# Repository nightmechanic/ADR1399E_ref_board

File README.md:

# ADR1399E Voltage reference circuit

This is a **hobby grade** 10V (well, close to...) voltage refernce based on Analog Devices' ADR1399E reference.
It can be powered with either 5V USB (using a boost switching regulator) , or a 5S Li-Ion pack (or equivalent)

*(Kicad rendering of the board)*

## Source:
Mostly based on: https://www.eevblog.com/forum/metrology/lm399-based-10-v-reference/ (specifically replies starting from 1300 to about 1343)

## Notes:
Designed in KiCad (9.0)

### Enclosure:
3D printable 2-piece enclosure design in [onshape](https://cad.onshape.com/documents/444727e948f9e5cc4e41eae1/w/781dc2eb3e355c2d7b923edf/e/b0f13c680a3e4fdfcef48c95?renderMode=0&rightPanel=namedPositionPanel&uiState=685cefcc24538942f7012c4b)

- Designed to use (4) M3x5x4 ("Voron") threaded inserts and (4) m3x20 screws for securing the base and lid together 
- With 4mm and 2mm Banana socket pairs
- With an (optional) internal refernce covers (identical top and bottom), to, somewhat, thermally isolate the refernce "island" from the rest 

Note that top/lid 3D printing may require supports for the screw head recesses
Printing the internal refernce cover will need supports

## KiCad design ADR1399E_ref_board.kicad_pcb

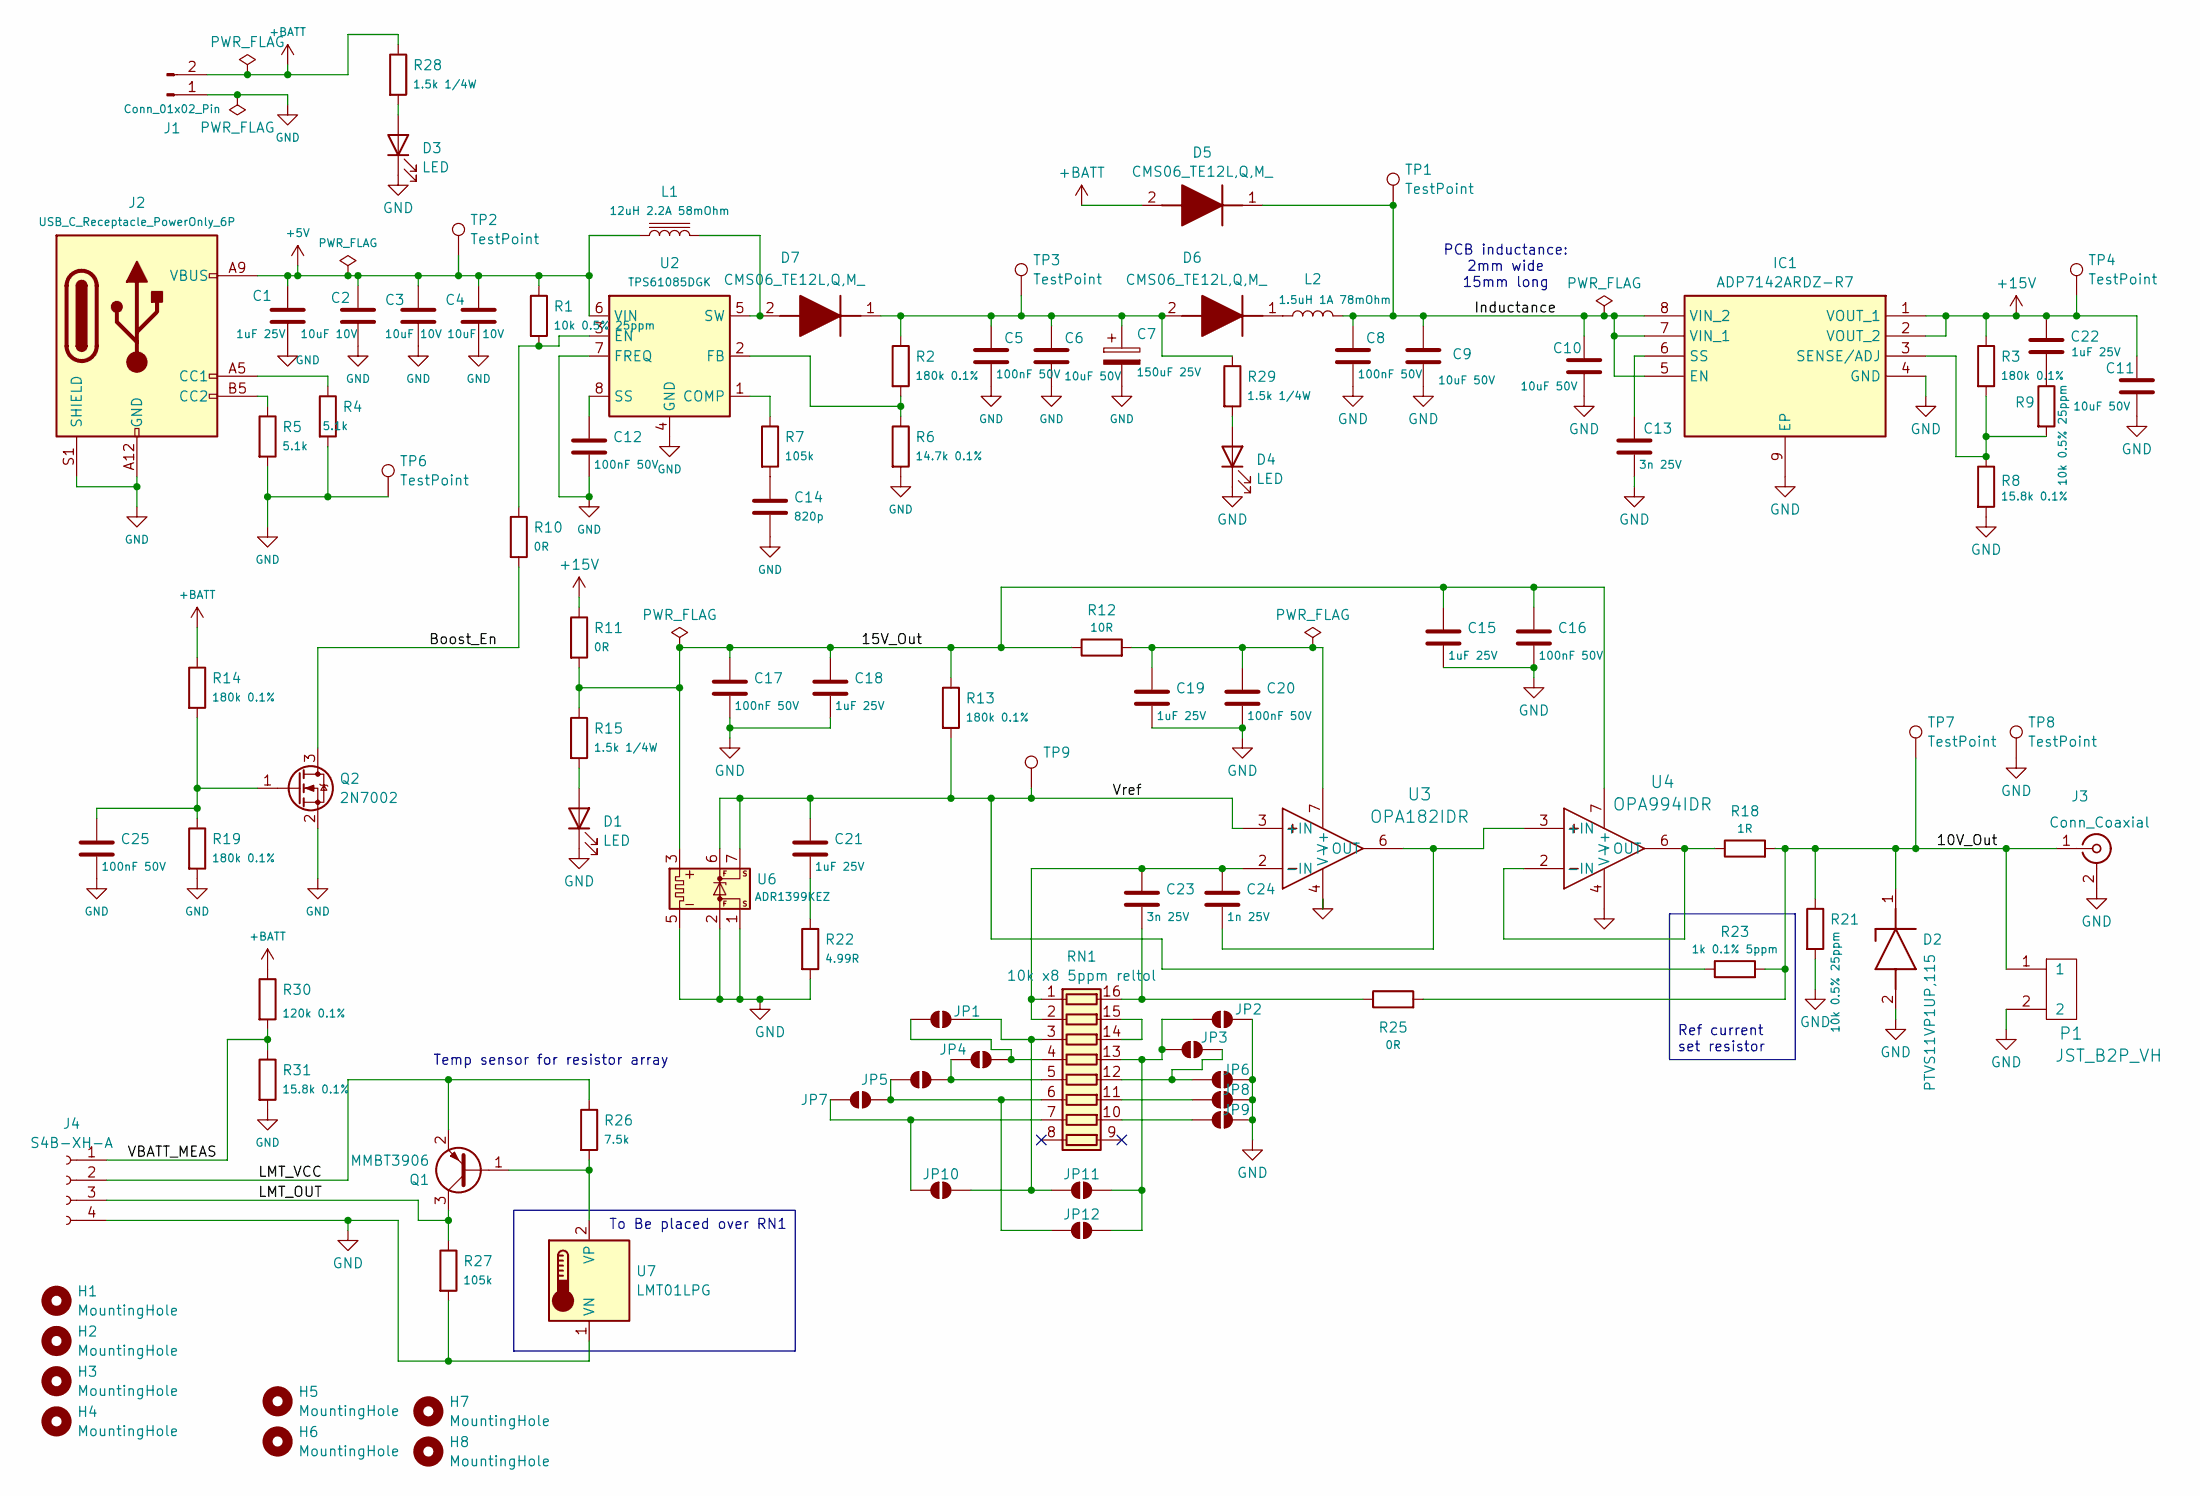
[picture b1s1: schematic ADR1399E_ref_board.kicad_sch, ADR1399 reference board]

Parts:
C1, C15, C18, C19, C21, C22: 1uF 25V; C_0603_1608Metric_Pad1.08x0.95mm_HandSolder; Manufacturer_Part_Number TMK107ABJ225KA-T
C2, C3, C4: 10uF 10V; C_0805_2012Metric_Pad1.18x1.45mm_HandSolder; Manufacturer_Part_Number CL21A106KPFNNNG
C5, C8, C12, C16, C17, C20, C25: 100nF 50V; C_0603_1608Metric_Pad1.08x0.95mm_HandSolder; Manufacturer_Part_Number CL10B104KB8NNWC
C6, C9, C10, C11: 10uF 50V; C_1210_3225Metric_Pad1.33x2.70mm_HandSolder; Manufacturer_Part_Number CL32A106KBJNNNE
C7: 150uF 25V; CP_Elec_8x6.7; Manufacturer_Part_Number A768KE157M1ELAE029
C13, C23: 3n 25V; C_0603_1608Metric_Pad1.08x0.95mm_HandSolder; Manufacturer_Part_Number GCM1885C1H302JA16D
C14: 820p; C_0603_1608Metric_Pad1.08x0.95mm_HandSolder; Manufacturer_Part_Number CC0603JRNPO9BN821
C24: 1n 25V; C_0603_1608Metric_Pad1.08x0.95mm_HandSolder; Manufacturer_Part_Number C0603C102J5GAC7411
D1, D3, D4: LED; LED_1206_3216Metric_Pad1.42x1.75mm_HandSolder; Manufacturer_Part_Number IN-S126ATA
D2: PTVS11VP1UP,115; PMEG3050EP115; Mouser Part Number 771-PTVS11VP1UP115
D5, D6, D7: CMS06_TE12L,Q,M_; SODFL4724X108N; Mouser Part Number 757-CMS06TE12L,Q,M
H1, H2, H3, H4: MountingHole; MountingHole_3.2mm_M3_ISO7380
H5, H6, H7, H8: MountingHole; MountingHole_2.2mm_M2
IC1: ADP7142ARDZ-R7; SOIC-8-1EP_3.9x4.9mm_P1.27mm_EP2.29x3mm_ThermalVias; Mouser Part Number 584-ADP7118ARDZ-R7
J1: Conn_01x02_Pin; AMASS_XT30PW-M_1x02_P2.50mm_Horizontal
J2: USB_C_Receptacle_PowerOnly_6P; USB_C_Receptacle_GCT_USB4125-xx-x-0190_6P_TopMnt_Horizontal; Manufacturer_Part_Number USB4125-GF-A-0190
J3: Conn_Coaxial; SMA_Molex_73251-1153_EdgeMount_Horizontal; Manufacturer_Part_Number 73251-1150
J4: S4B-XH-A; JST_XH_S4B-XH-A-1_1x04_P2.50mm_Horizontal; Manufacturer_Part_Number S4B-XH-A-GU
JP1, JP2, JP3, JP4, JP5, JP6, JP7, JP8, JP9, JP10, JP11, JP12: SolderJumper_2_Open; SolderJumper-2_P1.3mm_Open_RoundedPad1.0x1.5mm
L1: 12uH 2.2A 58mOhm; ASPI-6045S; Manufacturer_Part_Number ASPI-6045S-120M-T
L2: 1.5uH 1A 78mOhm; L_1210_3225Metric_Pad1.42x2.65mm_HandSolder; Manufacturer_Part_Number LBC3225T1R5MR
P1: JST_B2P_VH; JST_VH_B2P-VH_1x02_P3.96mm_Vertical; Manufacturer_Part_Number B2P-VH-GU
Q1: MMBT3906; SOT-23; Manufacturer_Part_Number MMBT3906LT1G
Q2: 2N7002; SOT-23
R1, R9, R21: 10k 0.5% 25ppm; R_0603_1608Metric_Pad0.98x0.95mm_HandSolder; Manufacturer_Part_Number MCT06030D1002DP500
R2, R3, R13, R14, R19: 180k 0.1%; R_0603_1608Metric_Pad0.98x0.95mm_HandSolder; Manufacturer_Part_Number ERA-3AEB184V
R4, R5: 5.1k; R_0603_1608Metric_Pad0.98x0.95mm_HandSolder; Manufacturer_Part_Number RG1608P-512-D-T5
R6: 14.7k 0.1%; R_0603_1608Metric_Pad0.98x0.95mm_HandSolder; Manufacturer_Part_Number ERA-3AEB1782V
R7, R27: 105k; R_0603_1608Metric_Pad0.98x0.95mm_HandSolder; Manufacturer_Part_Number RT0603DRD07105KL
R8: 15.8k 0.1%; R_0603_1608Metric_Pad0.98x0.95mm_HandSolder; Manufacturer_Part_Number RG1608P-512-D-T5
R10, R11, R25: 0R; R_0805_2012Metric_Pad1.20x1.40mm_HandSolder; Manufacturer_Part_Number MCU0805MZ0000ZP500
R12: 10R; R_0805_2012Metric_Pad1.20x1.40mm_HandSolder; Manufacturer_Part_Number RR1220Q-100-D
R15, R28, R29: 1.5k 1/4W; R_1206_3216Metric_Pad1.30x1.75mm_HandSolder; Manufacturer_Part_Number RNCP1206FTD1K50
R18: 1R; R_0805_2012Metric_Pad1.20x1.40mm_HandSolder; Manufacturer_Part_Number RT0805BRD071RL
R22: 4.99R; R_0603_1608Metric_Pad0.98x0.95mm_HandSolder; Manufacturer_Part_Number RT0603DRE074R99L
R23: 1k 0.1% 5ppm; R_0603_1608Metric_Pad0.98x0.95mm_HandSolder; Manufacturer_Part_Number PCF0603-13-1K0BT1
R26: 7.5k; R_0603_1608Metric_Pad0.98x0.95mm_HandSolder; Manufacturer_Part_Number RT0603FRE077K5L
R30: 120k 0.1%; R_0603_1608Metric_Pad0.98x0.95mm_HandSolder; Manufacturer_Part_Number ERA-3AEB124V
R31: 15.8k 0.1%; R_0603_1608Metric_Pad0.98x0.95mm_HandSolder; Manufacturer_Part_Number ERA-3AEB1782V
RN1: 10k x8 5ppm reltol; SO-16_3.9x9.9mm_P1.27mm; Manufacturer_Part_Number NOMCT16031002AT1
TP1, TP2, TP3, TP4, TP6, TP7, TP8, TP9: TestPoint; TestPoint_Loop_D1.80mm_Drill1.0mm_Beaded
U2: TPS61085DGK; VSSOP-8_3x3mm_P0.65mm; Manufacturer_Part_Number TPS61085DGKR
U3: OPA182IDR; D0008A-IPC_A; Manufacturer_Part_Number OPA182IDR
U4: OPA994IDR; D0008A-IPC_A; Manufacturer_Part_Number OPA994IDR
U6: ADR1399KEZ; Analog_LCC-8_5x5mm_P1.27mm; Manufacturer_Part_Number ADR1399KEZ
U7: LMT01LPG; LMT01LPG_LPG0002A; Manufacturer_Part_Number LMT01LPGM

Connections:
+5V: C1.1, C2.1, C3.1, C4.1, J2.A9 (VBUS), J2.B9 (VBUS), L1.1, R1.1, TP2.1, U2.6 (VIN)
+15V: C11.1, C22.1, IC1.1 (VOUT_1), IC1.2 (VOUT_2), R3.1, R11.1, TP4.1
+BATT: D5.2 (A), J1.2, R14.1, R28.1, R30.1
/10V_Out: D2.1 (K), J3.1 (In), P1.1, R18.2, R21.1, R23.2, R25.2, TP7.1
/15V_Out: C15.1, C16.1, C17.1, C18.1, R11.2, R12.1, R13.1, R15.1, U4.7 (V+), U6.3 (HEATER+)
/Boost_En: Q2.3 (D), R10.2
/Inductance: C8.1, C9.1, C10.1, D5.1 (K), IC1.5 (EN), IC1.7 (VIN_1), IC1.8 (VIN_2), L2.2, TP1.1
/LMT_OUT: J4.3, Q1.3 (C), R27.1
/LMT_VCC: J4.2, Q1.2 (E), R26.1
/VBATT_MEAS: J4.1, R30.2, R31.1
/Vref: C21.1, R13.2, R23.1, TP9.1, U3.3 (+IN), U6.6 (+REFF), U6.7 (+REFS)
GND: C1.2, C2.2, C3.2, C4.2, C5.2, C6.2, C7.2, C8.2, C9.2, C10.2, C11.2, C12.2, C13.2, C14.2, C15.2, C16.2, C17.2, C18.2, C19.2, C20.2, C25.2, D1.1 (K), D2.2 (A), D3.1 (K), D4.1 (K), IC1.4 (GND), IC1.9 (EP), J1.1, J2.A12 (GND), J2.B12 (GND), J2.S1 (SHIELD), J3.2 (Ext), J4.4, JP2.2 (B), JP6.2 (B), JP8.2 (B), JP9.2 (B), P1.2, Q2.2 (S), R4.2, R5.2, R6.2, R8.2, R19.2, R21.2, R22.2, R27.2, R31.2, TP6.1, TP8.1, U2.4 (GND), U2.7 (FREQ), U3.4 (V-), U4.4 (V-), U6.1 (-REFS), U6.2 (-REFF), U6.5 (HEATER-), U7.1 (VN)
unnamed: C14.1, R7.2
unnamed: C21.2, R22.1
unnamed: C22.2, R9.1
unnamed: D1.2 (A), R15.2
unnamed: D3.2 (A), R28.2
unnamed: D4.2 (A), R29.2
unnamed: C5.1, C6.1, C7.1, D6.2 (A), D7.1 (K), R2.1, R29.1, TP3.1
unnamed: D6.1 (K), L2.1
unnamed: D7.2 (A), L1.2, U2.5 (SW)
unnamed: IC1.3 (SENSE/ADJ), R3.2, R8.1, R9.2
unnamed: C13.1, IC1.6 (SS)
unnamed: J2.A5 (CC1), R4.1
unnamed: J2.B5 (CC2), R5.1
unnamed: JP1.1 (A), JP4.2 (B), RN1.4 (R4.1)
unnamed: JP1.2 (B), JP10.2 (B), JP11.1 (A), RN1.3 (R3.1)
unnamed: JP3.2 (B), JP6.1 (A), RN1.12 (R5.2)
unnamed: JP4.1 (A), JP5.2 (B), RN1.5 (R5.1)
unnamed: JP8.1 (A), RN1.11 (R6.2)
unnamed: JP9.1 (A), RN1.10 (R7.2)
unnamed: JP7.1 (A), JP10.1 (A), RN1.7 (R7.1)
unnamed: JP2.1 (A), JP3.1 (A), JP11.2 (B), JP12.2 (B), RN1.13 (R4.2)
unnamed: JP5.1 (A), JP7.2 (B), JP12.1 (A), RN1.6 (R6.1)
unnamed: Q1.1 (B), R26.2, U7.2 (VP)
unnamed: C25.1, Q2.1 (G), R14.2, R19.1
unnamed: C23.1, C24.1, RN1.1 (R1.1), RN1.2 (R2.1), U3.2 (-IN)
unnamed: C23.2, R25.1, RN1.16 (R1.2)
unnamed: RN1.14 (R3.2), RN1.15 (R2.2)
unnamed: R7.1, U2.1 (COMP)
unnamed: R1.2, R10.1, U2.3 (EN)
unnamed: R2.2, R6.1, U2.2 (FB)
unnamed: C12.1, U2.8 (SS)
unnamed: C24.2, U3.6 (OUT), U4.3 (+IN)
unnamed: C19.1, C20.1, R12.2, U3.7 (V+)
unnamed: R18.1, U4.2 (-IN), U4.6 (OUT)

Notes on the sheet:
PCB inductance: 2mm wide 15mm long
Temp sensor for resistor array
Ref current set resistor
To Be placed over RN1

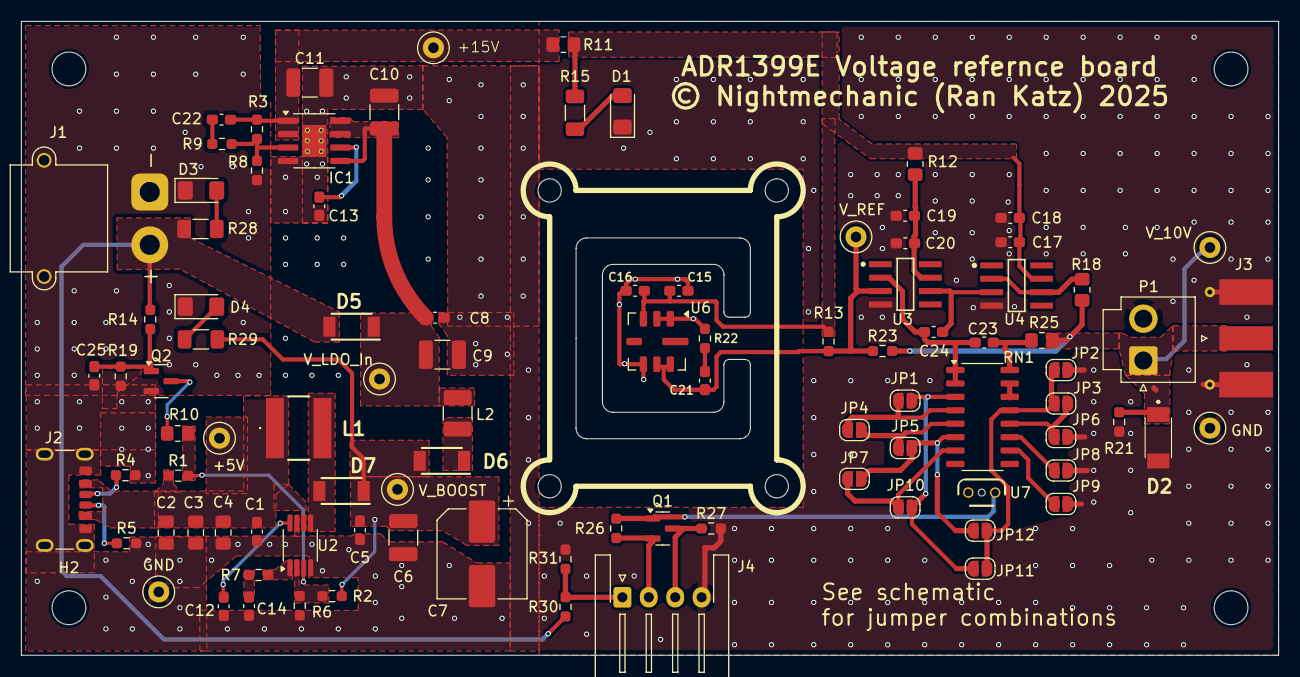
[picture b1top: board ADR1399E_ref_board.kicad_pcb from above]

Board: 4 copper layers, 119.0 x 60.0 mm, 103 parts (0 on the bottom side), 46 nets.

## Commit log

2025-05-19 moving forward
2025-05-25 getting closer
2025-05-25 complete schematics?
2025-06-04 buffered output, temp sensor, resistor network
2025-06-04 added schematic pdf
2025-06-08 Final BOM (?)
2025-06-08 started layout
2025-06-09 more layout prep
2025-06-09 3d model and footprint updates
2025-06-09 more 3d model updates
2025-06-09 more layout
2025-06-10 widen USB connector slots
2025-06-10 interV1
2025-06-10 maybe power done
2025-06-11 Reference Island formed!
2025-06-11 initial amp placement
    initial amp placement
    Added Vbatt divider
2025-06-11 cleanup
2025-06-11 more cleanup
2025-06-12 copper balancing
2025-06-12 moved from lt3042 to adp7118
2025-06-12 updated PCB to adp7118/42
2025-06-12 changed to 15V, adp7142
2025-06-15 Replaced Boost enable comparator with N-MOS
    also changed Vbatt divider resistor value
2025-06-15 Update README.md
    typo
2025-06-18 bended temp sensor model
2025-06-19 moved VH connector to center
    avoid collision with Banana sockets (in case)
2025-06-25 really centered the VH connector
    And added VH housing 3d model
2025-06-26 moved USB connector a bit
    better enclosure fit
2025-06-26 Update README.md
    image path correction
2025-07-06 Updated sllkscreen (logo etc.)

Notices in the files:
ADR1399E_ref_board.kicad_pcb:
© Nightmechanic (Ran Katz) 2025
© Nightmechanic 2025
